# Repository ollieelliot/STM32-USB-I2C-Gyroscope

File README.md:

# STM32-USB-I2C-Gyroscope
Connecting an STM32F405RG microcontroller with a gyroscope through I2C as well as connecting USB B Micro, SWD and USART in order to learn more about circuit and PCB design.

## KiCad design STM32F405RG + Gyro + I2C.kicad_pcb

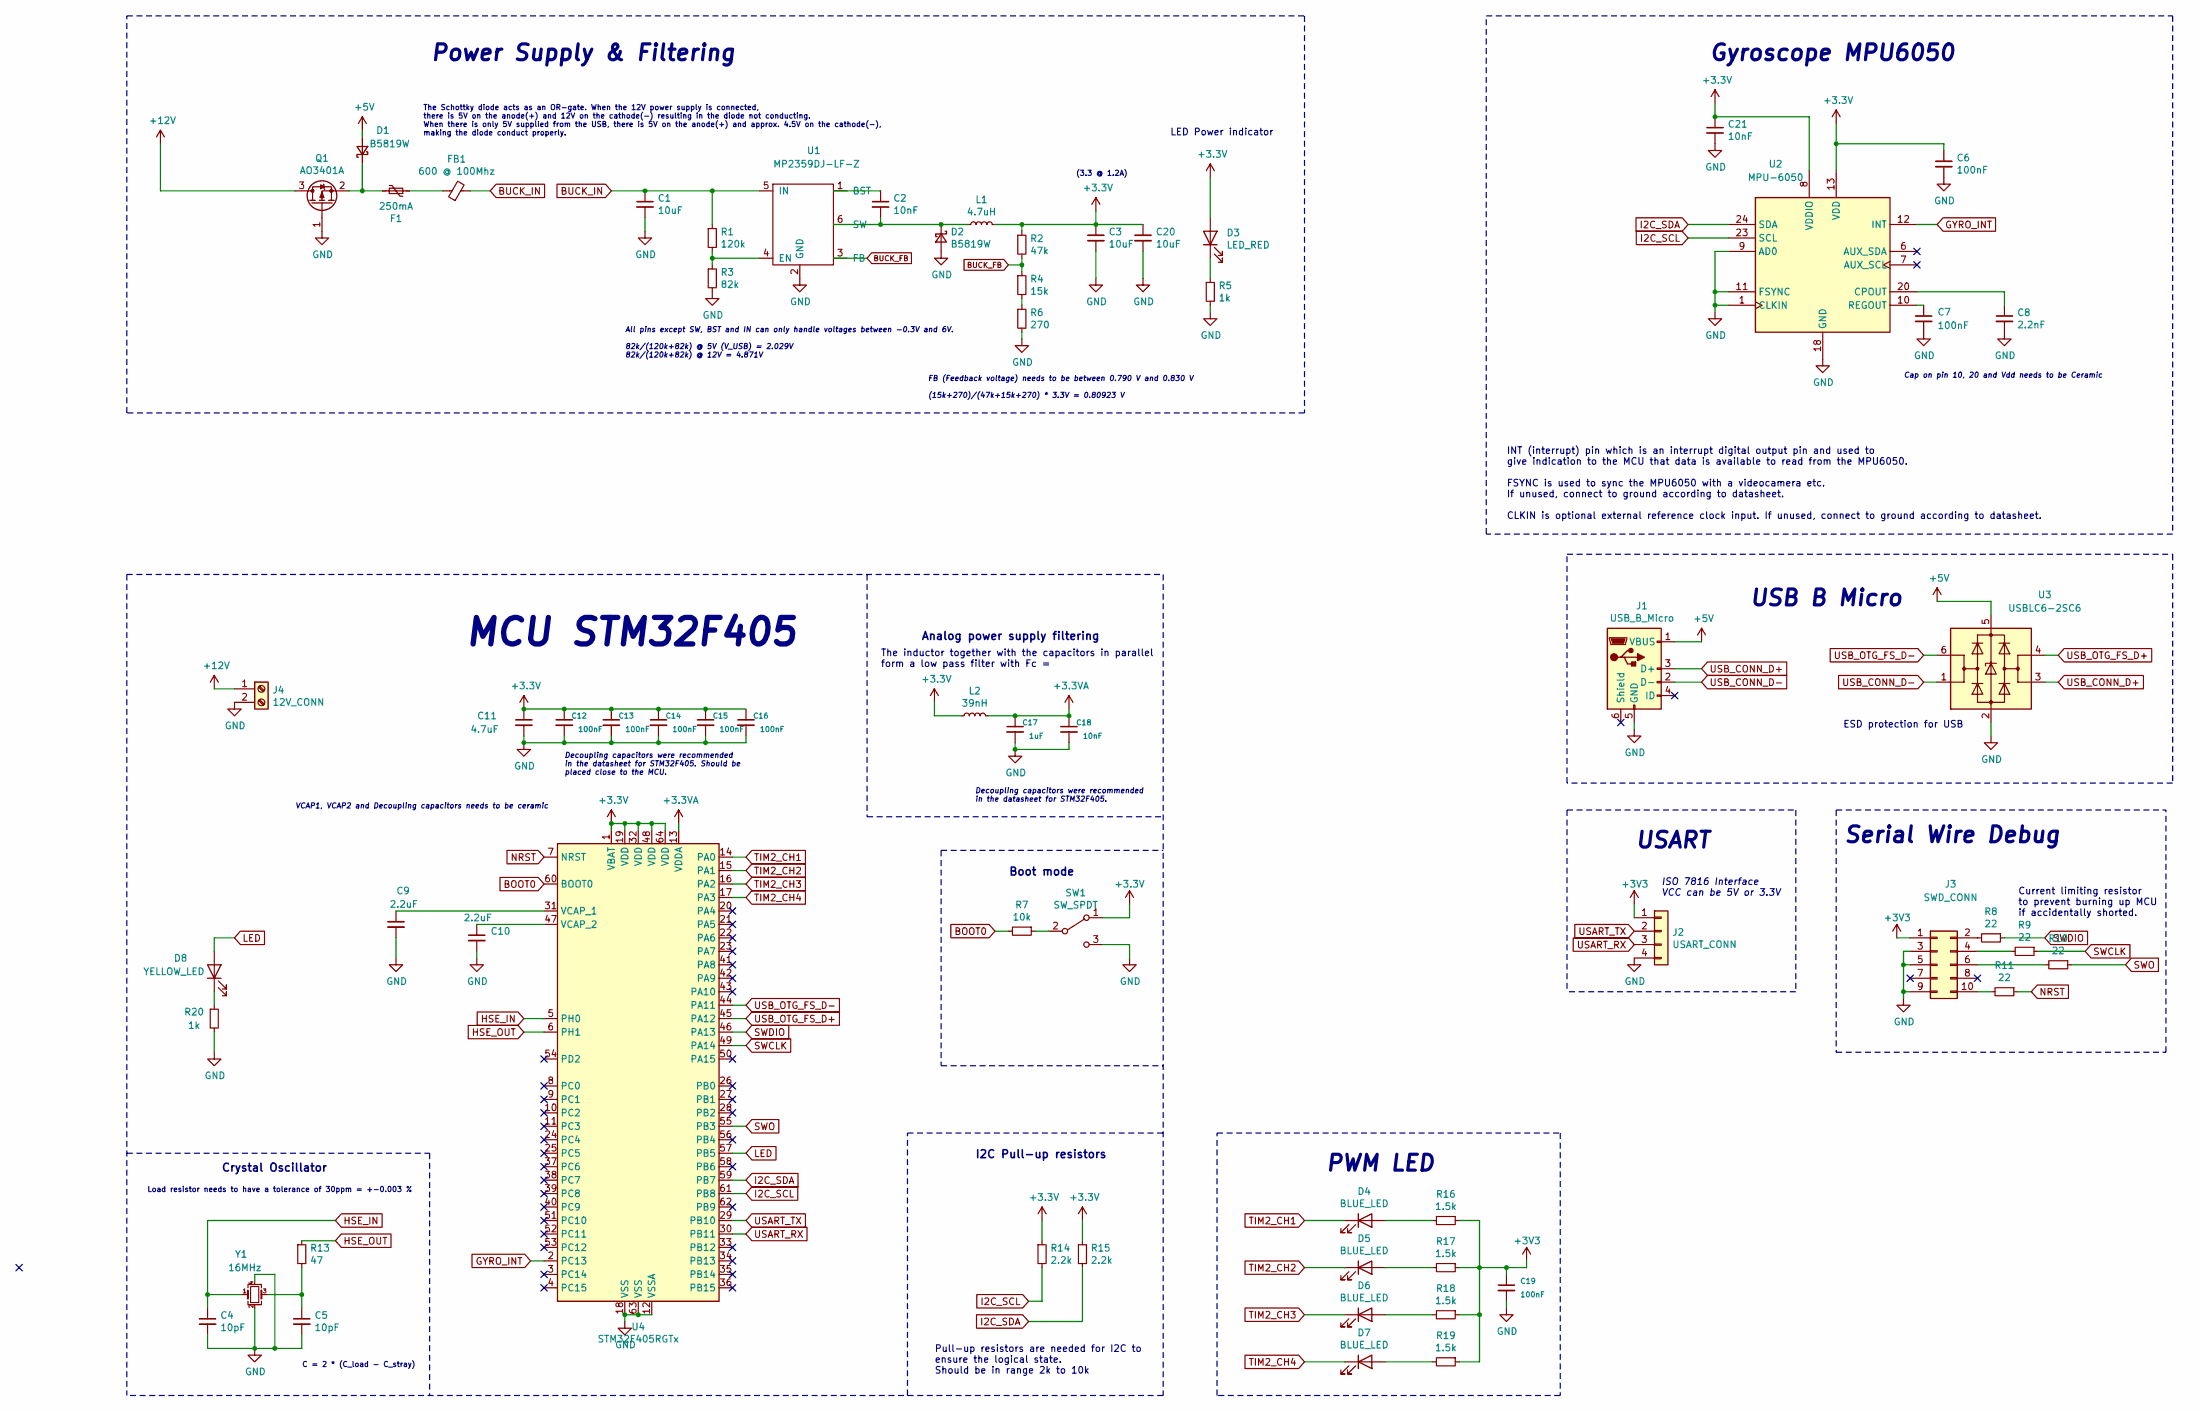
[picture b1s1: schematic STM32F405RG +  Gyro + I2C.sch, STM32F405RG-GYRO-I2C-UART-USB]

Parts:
C1, C3, C20: 10uF; C_1206_3216Metric; LCSC C13585
C2, C21: 10nF; C_0603_1608Metric; LCSC C57112
C4, C5: 10pF; C_0402_1005Metric; LCSC C32949
C6, C12, C13, C14, C15, C16, C19: 100nF; C_0402_1005Metric; LCSC C1525
C7: 100nF; C_0603_1608Metric; LCSC C14663
C8: 2.2nF; C_0603_1608Metric; LCSC C1604
C9, C10: 2.2uF; C_0603_1608Metric; LCSC C23630
C11: 4.7uF; C_0603_1608Metric; LCSC C19666
C17: 1uF; C_0402_1005Metric; LCSC C52923
C18: 10nF; C_0402_1005Metric; LCSC C15195
D1, D2: B5819W; D_SOD-123; LCSC C8598
D3: LED_RED; LED_0603_1608Metric; LCSC C2286
D4, D5, D6, D7: BLUE_LED; LED_0603_1608Metric; LCSC C72041
D8: YELLOW_LED; LED_0603_1608Metric; LCSC C72038
F1: 250mA; Fuse_1206_3216Metric; LCSC C369159
FB1: 600 @ 100Mhz; L_0805_2012Metric; LCSC C1017
J1: USB_B_Micro; USB_Micro-B_Molex-105017-0001
J2: USART_CONN; Molex_PicoBlade_53048-0410_1x04_P1.25mm_Horizontal
J3: SWD_CONN; PinHeader_2x05_P1.27mm_Vertical_SMD
J4: 12V_CONN; TerminalBlock_Phoenix_PT-1,5-2-5.0-H_1x02_P5.00mm_Horizontal
L1: 4.7uH; L_Sunlord_MWSA0518_5.4x5.2mm; LCSC C408347
L2: 39nH; L_0402_1005Metric; LCSC C26443
Q1: AO3401A; SOT-23; LCSC C15127
R1: 120k; R_0603_1608Metric; LCSC C25808
R2: 47k; R_0603_1608Metric; LCSC C25819
R3: 82k; R_0603_1608Metric; LCSC C23254
R4: 15k; R_0603_1608Metric; LCSC C22809
R5: 1k; R_0603_1608Metric; LCSC C369159
R6: 270; R_0603_1608Metric; LCSC C22966
R7: 10k; R_0402_1005Metric; LCSC C25744
R8, R9, R10, R11: 22; R_0402_1005Metric; LCSC C25092
R13: 47; R_0402_1005Metric; LCSC C25118
R14, R15: 2.2k; R_0402_1005Metric; LCSC C25879
R16, R17, R18, R19: 1.5k; R_0402_1005Metric; LCSC C25867
R20: 1k; R_0402_1005Metric; LCSC C21190
SW1: SW_SPDT; SW_SPDT_PCM12
U1: MP2359DJ-LF-Z; SOT-23-6; LCSC C14259
U2: MPU-6050; InvenSense_QFN-24_4x4mm_P0.5mm; LCSC C24112
U3: USBLC6-2SC6; SOT-23-6; LCSC C7519
U4: STM32F405RGTx; LQFP-64_10x10mm_P0.5mm; LCSC C15742
Y1: 16MHz; Crystal_SMD_3225-4Pin_3.2x2.5mm; LCSC C13738

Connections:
+3.3VA: C17.1, C18.1, L2.2, U4.13 (VDDA)
+5V: D1.2 (A), J1.1 (VBUS), U3.5 (VBUS)
+12V: J4.1, Q1.3 (D)
BOOT0: R7.2, U4.60 (BOOT0)
BUCK_FB: R2.2, R4.1, U1.3 (FB)
BUCK_IN: C1.1, FB1.2, R1.1, U1.5 (IN)
GND: C1.2, C3.2, C4.2, C5.2, C6.2, C7.2, C8.2, C9.2, C10.2, C11.2, C12.2, C13.2, C14.2, C15.2, C16.2, C17.2, C18.2, C19.2, C20.2, C21.2, D2.2 (A), J1.5 (GND), J2.4, J3.3, J3.5, J3.9, J4.2, Q1.1 (G), R3.2, R5.2, R6.2, R20.2, SW1.3 (C), U1.2 (GND), U2.1 (CLKIN), U2.9 (AD0), U2.11 (FSYNC), U2.18 (GND), U3.2 (GND), U4.12 (VSSA), U4.18 (VSS), U4.63 (VSS), Y1.2, Y1.4
GYRO_INT: U2.12 (INT), U4.2 (PC13)
HSE_IN: C4.1, U4.5 (PH0), Y1.1
HSE_OUT: R13.1, U4.6 (PH1)
I2C_SCL: R14.2, U2.23 (SCL), U4.61 (PB8)
I2C_SDA: R15.2, U2.24 (SDA), U4.59 (PB7)
LED: D8.2 (A), U4.57 (PB5)
NRST: R11.1, U4.7 (NRST)
unnamed: C2.1, U1.1 (BST)
unnamed: C2.2, D2.1 (K), L1.1, U1.6 (SW)
unnamed: C5.1, R13.2, Y1.3
unnamed: C7.1, U2.10 (REGOUT)
unnamed: C8.1, U2.20 (CPOUT)
unnamed: C9.1, U4.31 (VCAP_1)
unnamed: C10.1, U4.47 (VCAP_2)
unnamed: D1.1 (K), F1.2, Q1.2 (S)
unnamed: D3.1 (K), R5.1
unnamed: D4.2 (A), R16.2
unnamed: D5.2 (A), R17.2
unnamed: D6.2 (A), R18.2
unnamed: D7.2 (A), R19.2
unnamed: D8.1 (K), R20.1
unnamed: F1.1, FB1.1
unnamed: J3.2, R8.2
unnamed: J3.4, R9.2
unnamed: J3.6, R10.2
unnamed: J3.10, R11.2
unnamed: R1.2, R3.1, U1.4 (EN)
unnamed: R4.2, R6.1
unnamed: R7.1, SW1.2 (B)
SWCLK: R9.1, U4.49 (PA14)
SWDIO: R8.1, U4.46 (PA13)
SWO: R10.1, U4.55 (PB3)
TIM2_CH1: D4.1 (K), U4.14 (PA0)
TIM2_CH2: D5.1 (K), U4.15 (PA1)
TIM2_CH3: D6.1 (K), U4.16 (PA2)
TIM2_CH4: D7.1 (K), U4.17 (PA3)
USART_RX: J2.3, U4.30 (PB11)
USART_TX: J2.2, U4.29 (PB10)
USB_CONN_D+: J1.3 (D+), U3.3 (I/O2)
USB_CONN_D-: J1.2 (D-), U3.1 (I/O1)
USB_OTG_FS_D+: U3.4 (I/O2), U4.45 (PA12)
USB_OTG_FS_D-: U3.6 (I/O1), U4.44 (PA11)

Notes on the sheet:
Pull-up resistors are needed for I2C to ensure the logical state. Should be in range 2k to 10k
INT (interrupt) pin which is an interrupt digital output pin and used to give indication to the MCU that data is available to read from the MPU6050. FSYNC is used to sync the MPU6050 with a videocamera etc. If unused, connect to ground according to datasheet. CLKIN is optional external reference cl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
LED Power indicator
Load resistor needs to have a tolerance of 30ppm = +-0.003 %
(3.3 @ 1.2A)
All pins except SW, BST and IN can only handle voltages between -0.3V and 6V. 82k/(120k+82k) @ 5V (V_USB) = 2.029V 82k/(120k+82k) @ 12V = 4.871V
The Schottky diode acts as an OR-gate. When the 12V power supply is connected, there is 5V on the anode(+) and 12V on the cathode(-) resulting in the diode not conducting. When there is only 5V supplied from the USB, there is 5V on the anode(+) and approx. 4.5V on the cathode(-), making the diode c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
Serial Wire Debug
Power Supply & Filtering
USB B Micro
MCU STM32F405
Current limiting resistor to prevent burning up MCU if accidentally shorted.
The inductor together with the capacitors in parallel form a low pass filter with Fc =
Analog power supply filtering
Decoupling capacitors were recommended in the datasheet for STM32F405.
Crystal Oscillator
I2C Pull-up resistors
Boot mode
Decoupling capacitors were recommended in the datasheet for STM32F405. Should be placed close to the MCU.
ISO 7816 Interface VCC can be 5V or 3.3V
USART
ESD protection for USB
C = 2 * (C_load - C_stray)
FB (Feedback voltage) needs to be between 0.790 V and 0.830 V (15k+270)/(47k+15k+270) * 3.3V = 0.80923 V
Cap on pin 10, 20 and Vdd needs to be Ceramic
VCAP1, VCAP2 and Decoupling capacitors needs to be ceramic
PWM LED
Gyroscope MPU6050

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
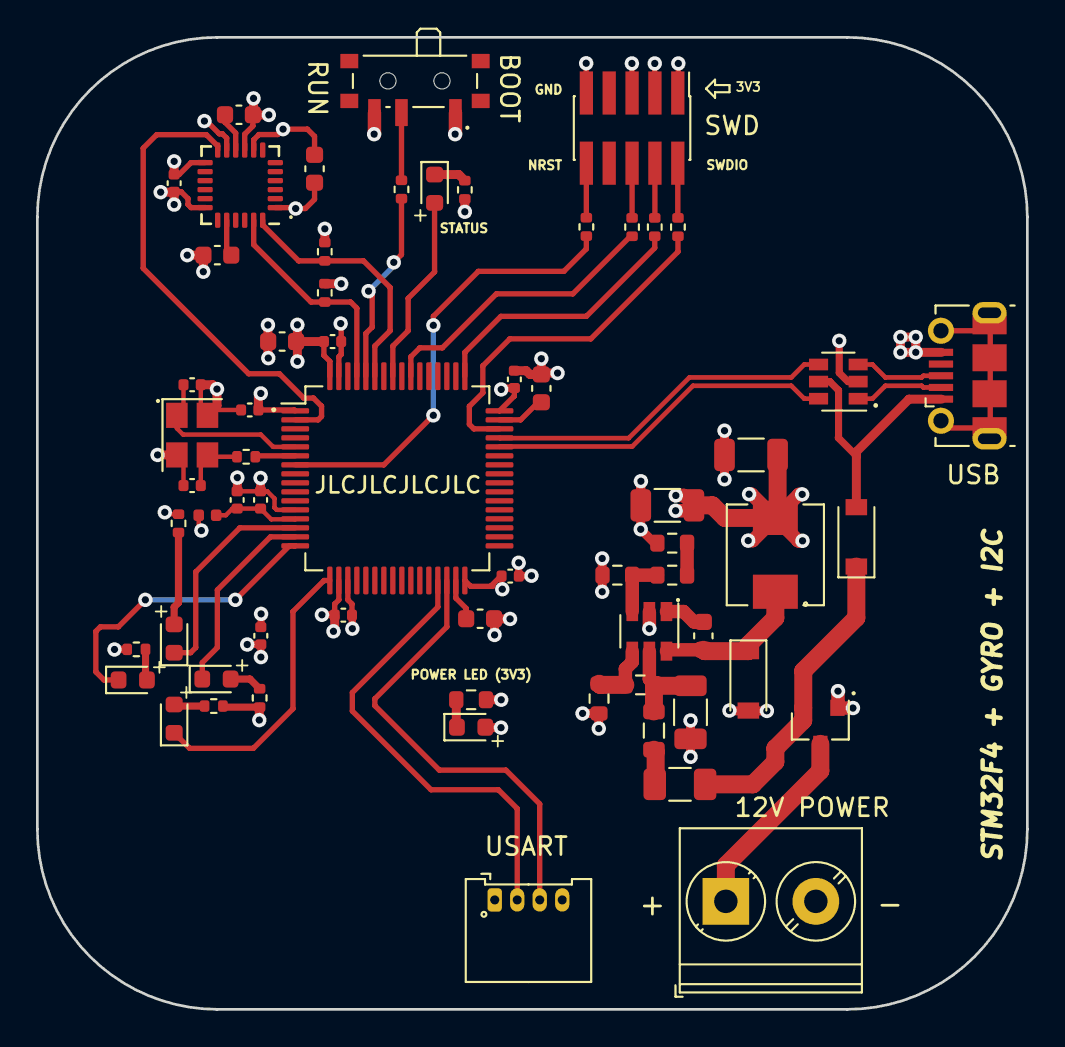
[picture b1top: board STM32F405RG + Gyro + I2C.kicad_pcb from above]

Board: 4 copper layers, 55.0 x 54.0 mm, 63 parts (0 on the bottom side), 50 nets.

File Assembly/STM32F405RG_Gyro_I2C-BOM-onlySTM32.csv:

Comment,Designator,Footprint,LCSC
"10uF","C1,C3,C20","Capacitor_SMD:C_1206_3216Metric",""
"4.7uF","C11","Capacitor_SMD:C_0603_1608Metric",""
"100nF","C6,C12,C13,C14,C15,C16,C19","Capacitor_SMD:C_0402_1005Metric",""
"1uF","C17","Capacitor_SMD:C_0402_1005Metric",""
"10nF","C18","Capacitor_SMD:C_0402_1005Metric",""
"10nF","C2,C21","Capacitor_SMD:C_0603_1608Metric",""
"10pF","C4,C5","Capacitor_SMD:C_0402_1005Metric",""
"100nF","C7","Capacitor_SMD:C_0603_1608Metric",""
"2.2nF","C8","Capacitor_SMD:C_0603_1608Metric",""
"2.2uF","C9,C10","Capacitor_SMD:C_0603_1608Metric",""
"B5819W","D1,D2","Diode_SMD:D_SOD-123",""
"LED_RED","D3","LED_SMD:LED_0603_1608Metric",""
"BLUE_LED","D4,D5,D6,D7","LED_SMD:LED_0603_1608Metric",""
"YELLOW_LED","D8","LED_SMD:LED_0603_1608Metric",""
"250mA","F1","Fuse:Fuse_1206_3216Metric",""
"600 @ 100Mhz","FB1","Inductor_SMD:L_0805_2012Metric",""
"USB_B_Micro","J1","USB Footprint Library:USB_Micro-B_Molex-105017-0001",""
"USART_CONN","J2","Connector_Molex:Molex_PicoBlade_53048-0410_1x04_P1.25mm_Horizontal",""
"SWD_CONN","J3","Connector_PinHeader_1.27mm:PinHeader_2x05_P1.27mm_Vertical_SMD",""
"12V_CONN","J4","TerminalBlock_Phoenix:TerminalBlock_Phoenix_PT-1,5-2-5.0-H_1x02_P5.00mm_Horizontal",""
"4.7uH","L1","Inductor_SMD:L_Sunlord_MWSA0518_5.4x5.2mm","C408347"
"39nH","L2","Inductor_SMD:L_0402_1005Metric",""
"AO3401A","Q1","Package_TO_SOT_SMD:SOT-23",""
"120k","R1","Resistor_SMD:R_0603_1608Metric",""
"47","R13","Resistor_SMD:R_0402_1005Metric",""
"2.2k","R14,R15","Resistor_SMD:R_0402_1005Metric",""
"1.5k","R16,R17,R18,R19","Resistor_SMD:R_0402_1005Metric",""
"47k","R2","Resistor_SMD:R_0603_1608Metric",""
"1k","R20","Resistor_SMD:R_0402_1005Metric",""
"82k","R3","Resistor_SMD:R_0603_1608Metric",""
"15k","R4","Resistor_SMD:R_0603_1608Metric",""
"1k","R5","Resistor_SMD:R_0603_1608Metric",""
"270","R6","Resistor_SMD:R_0603_1608Metric",""
"10k","R7","Resistor_SMD:R_0402_1005Metric",""
"22","R8,R9,R10,R11","Resistor_SMD:R_0402_1005Metric",""
"SW_SPDT","SW1","Button_Switch_SMD:SW_SPDT_PCM12",""
"MP2359DJ-LF-Z","U1","Package_TO_SOT_SMD:SOT-23-6",""
"MPU-6050","U2","Sensor_Motion:InvenSense_QFN-24_4x4mm_P0.5mm","C24112"
"USBLC6-2SC6","U3","Package_TO_SOT_SMD:SOT-23-6",""
"STM32F405RGTx","U4","Package_QFP:LQFP-64_10x10mm_P0.5mm","C15742"
"16MHz","Y1","Crystal:Crystal_SMD_3225-4Pin_3.2x2.5mm",""

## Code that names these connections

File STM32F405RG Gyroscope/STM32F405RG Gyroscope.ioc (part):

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Mcu.Name=STM32F405RGTx
Mcu.Package=LQFP64
Mcu.UserName=STM32F405RGTx
PA0-WKUP.Signal=S_TIM2_CH1_ETR
PA1.Signal=S_TIM2_CH2
PA11.Mode=Device_Only
PA11.Signal=USB_OTG_FS_DM
PA12.Mode=Device_Only
PA12.Signal=USB_OTG_FS_DP
PA13.Mode=Trace_Asynchronous_SW
PA13.Signal=SYS_JTMS-SWDIO
PA14.Mode=Trace_Asynchronous_SW
PA14.Signal=SYS_JTCK-SWCLK
PA2.Signal=S_TIM2_CH3
PA3.Signal=S_TIM2_CH4
PA4.GPIOParameters=GPIO_Label
PA4.GPIO_Label=GYRO_CS
PA4.Signal=GPIO_Output
PB10.Mode=Asynchronous
PB10.Signal=USART3_TX
PB11.Mode=Asynchronous
PB11.Signal=USART3_RX
PB3.Mode=Trace_Asynchronous_SW
PB3.Signal=SYS_JTDO-SWO
PB5.GPIOParameters=GPIO_Label
PB5.GPIO_Label=LED
PB5.Signal=GPIO_Output
PB6.Mode=I2C
PB6.Signal=I2C1_SCL
PB7.Mode=I2C
PB7.Signal=I2C1_SDA
PC4.GPIOParameters=GPIO_Label
PC4.GPIO_Label=MPU6050_INT
PC4.Signal=GPIO_Input
PH0-OSC_IN.Mode=HSE-External-Oscillator
PH0-OSC_IN.Signal=RCC_OSC_IN
PH1-OSC_OUT.Mode=HSE-External-Oscillator
PH1-OSC_OUT.Signal=RCC_OSC_OUT
RCC.HSE_VALUE=25000000
RCC.SYSCLKFreq_VALUE=16000000
board=custom

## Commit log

2021-09-10 Upload files
2021-09-12 Added more things to the circuit
2021-09-12 Added more things to circuit
2021-09-14 Added annotations
2021-09-15 Started PCB layout
2021-09-16 Minor changes
2021-09-16 Changed power supply layout
2021-09-17 Uploaded new PDF of the the latest schematic
2021-09-18 Changes & PCB routing
    Changed pin on LED, started routing signals and differential pairs
2021-09-18 Revert "Changes & PCB routing"
    This reverts commit bada82a912c55c4199179019eb8492b380a79c23, reversing
    changes made to f585d00e69f4fe89e0924f05bd4fcbc467184eeb.
2021-09-19 Fixed layout and added text to silkscreen
2021-09-19 Changes
    FIX: Changed SWD connector from socket to header
2021-09-20 Added BOM file
2021-09-20 Changed gyroscope, added gerber and assembly files
    -Changed Gyroscope from MPU-6000 to MPU-6050
    -Added Gerber and Assembly files
2021-10-18 Refreshed files
